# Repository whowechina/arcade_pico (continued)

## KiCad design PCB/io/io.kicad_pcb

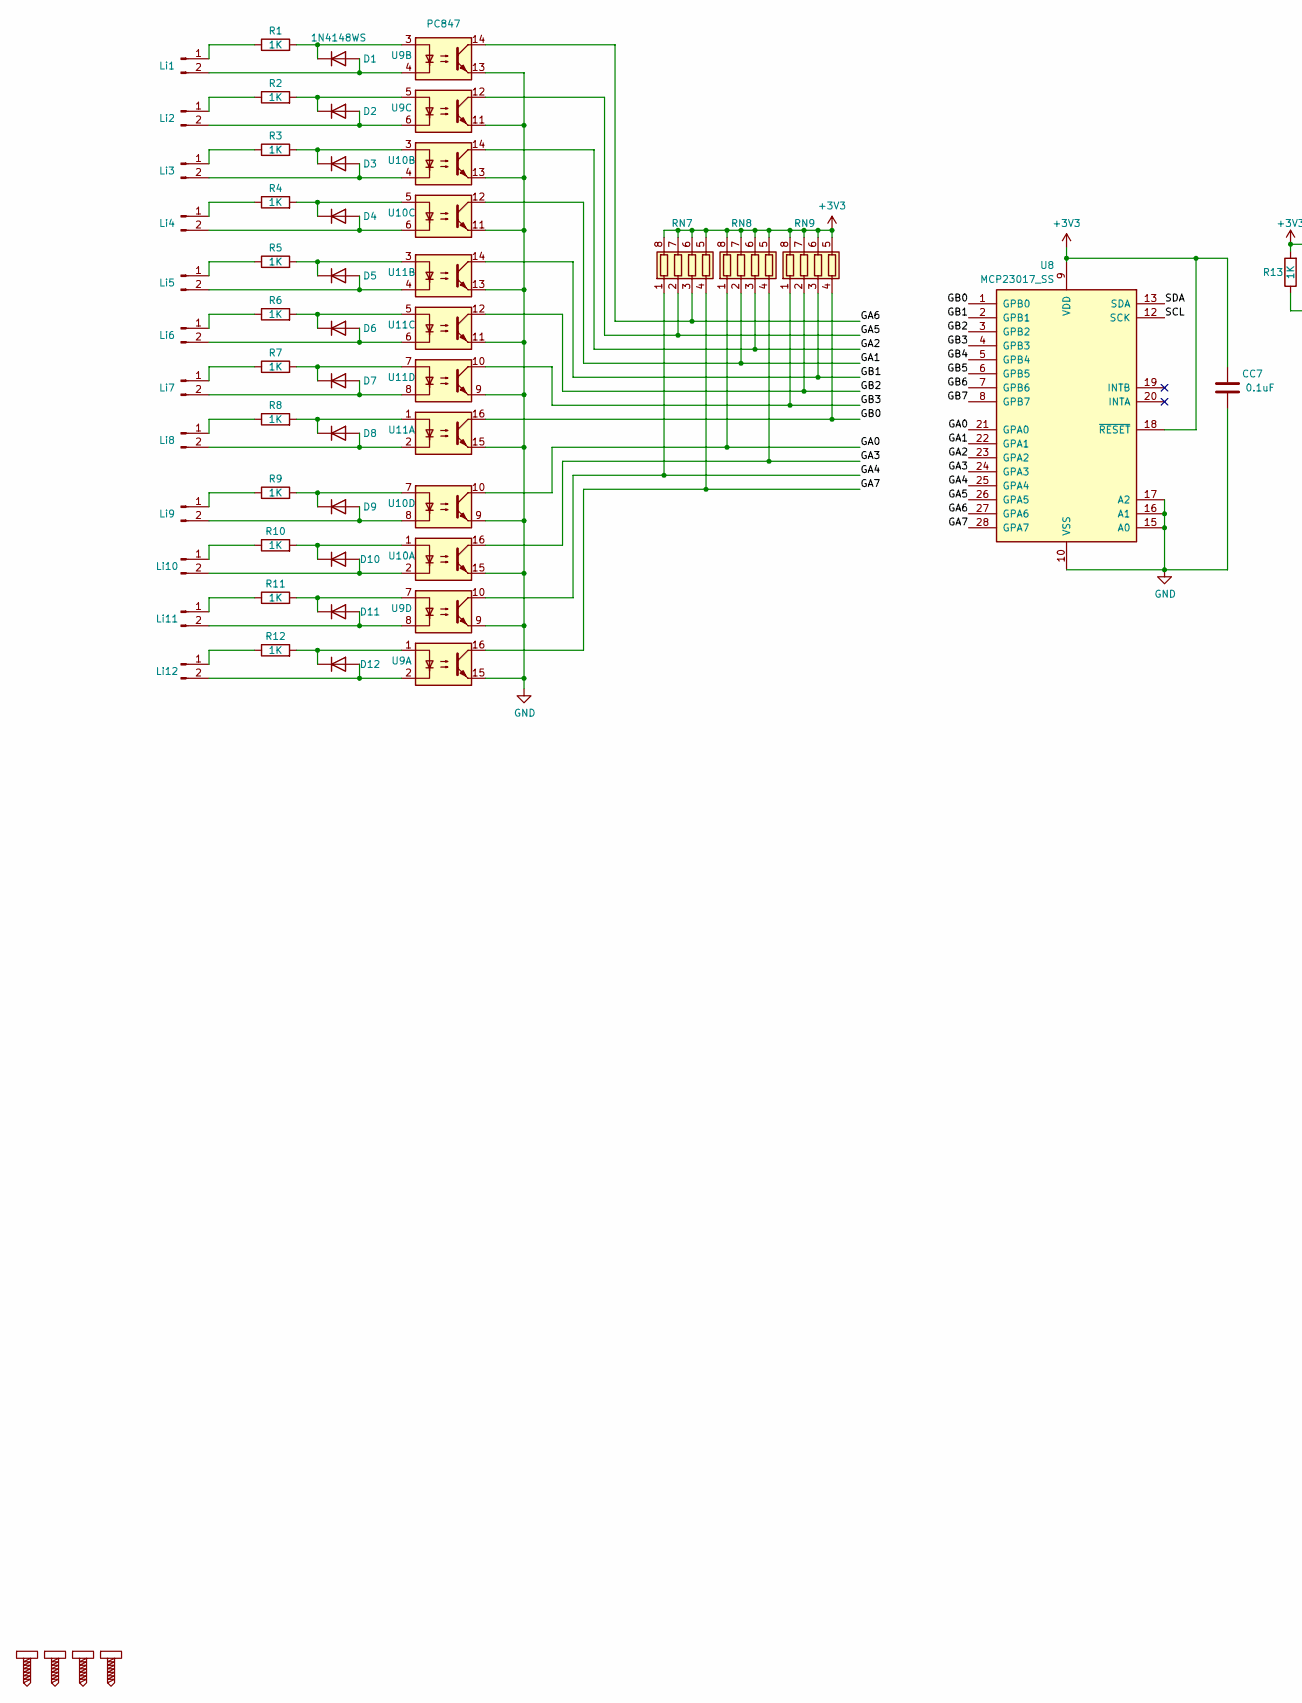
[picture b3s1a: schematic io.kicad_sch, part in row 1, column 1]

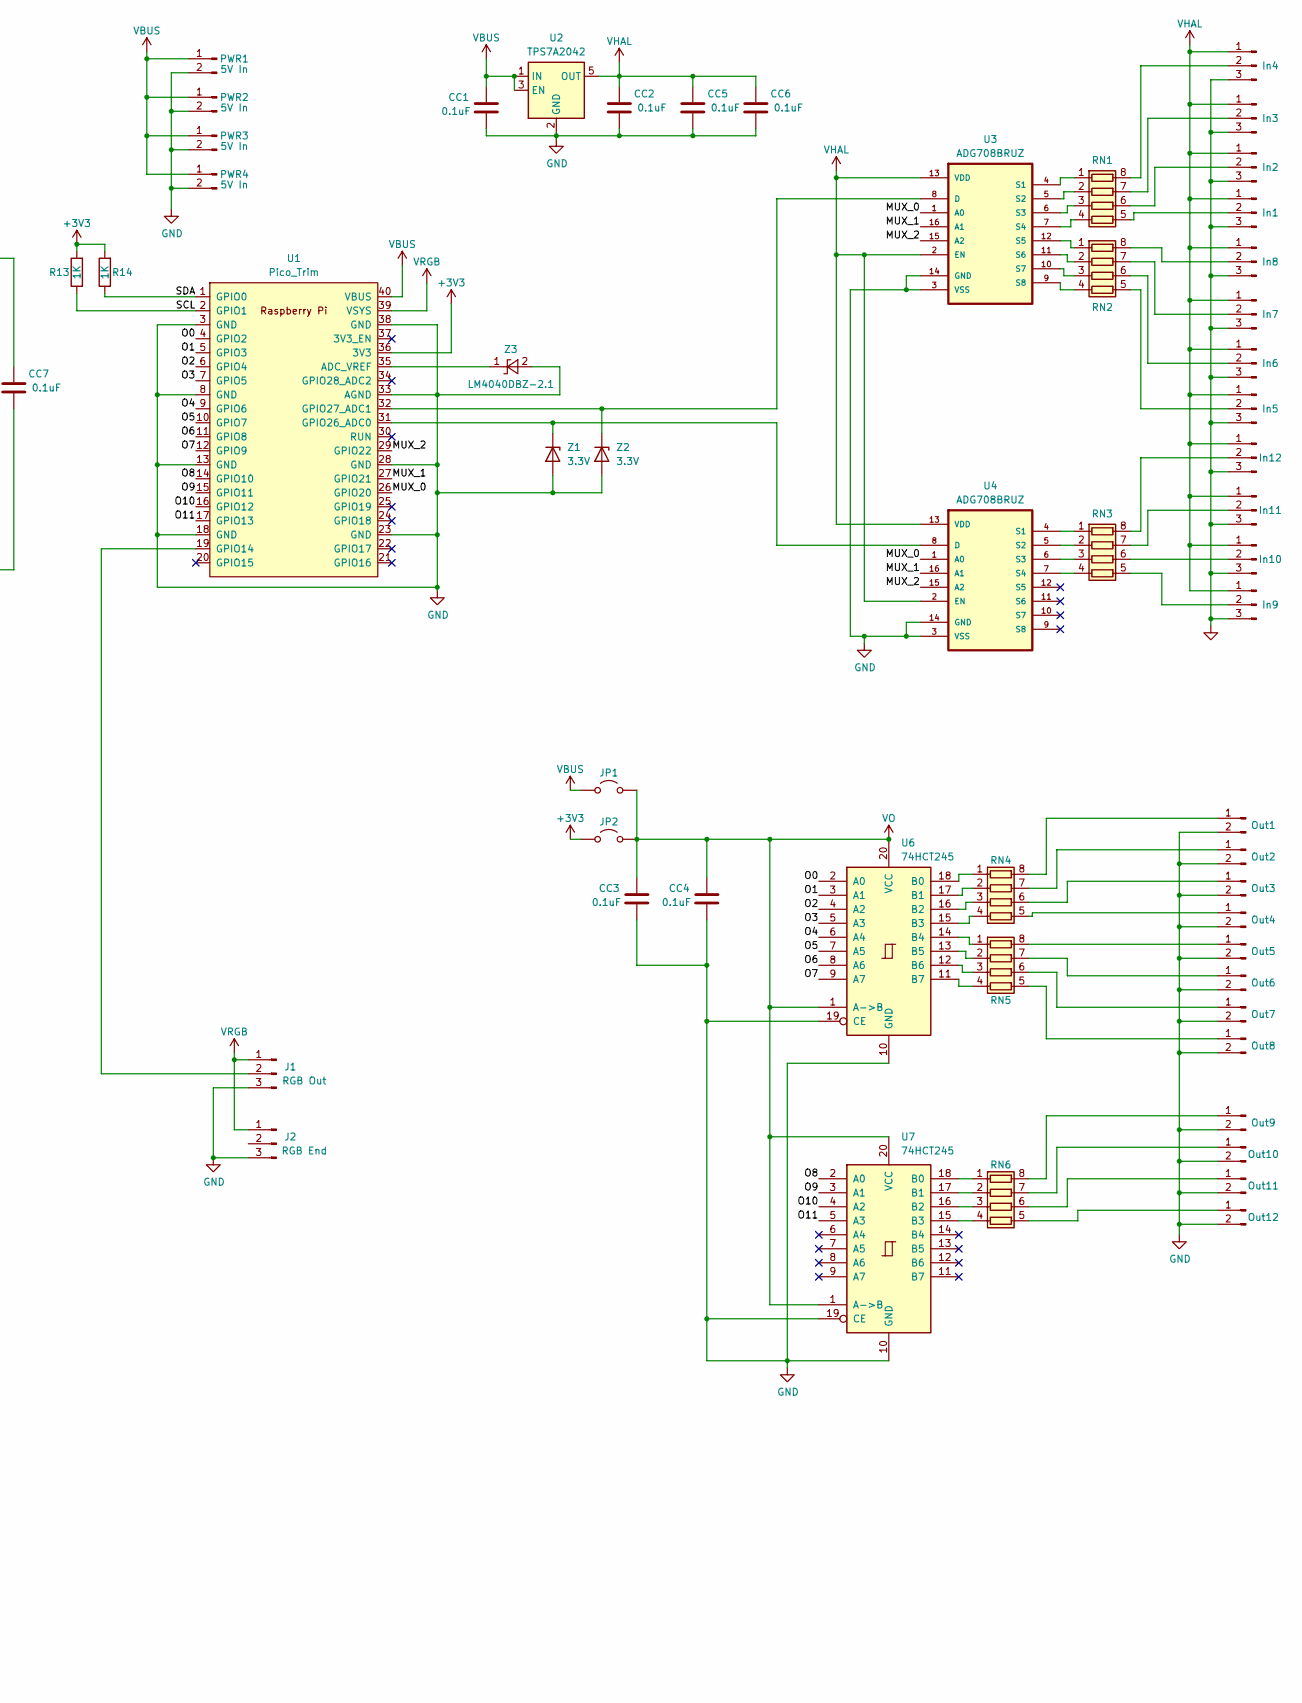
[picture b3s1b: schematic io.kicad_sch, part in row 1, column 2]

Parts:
CC1, CC2, CC3, CC4, CC5, CC6, CC7: 0.1uF; C_0603_1608Metric_Pad1.08x0.95mm_HandSolder
D1, D2, D3, D4, D5, D6, D7, D8, D9, D10, D11, D12: 1N4148WS; D_SOD-323_FAT
In1, In2, In3, In4, In5, In6, In7, In8, In9, In10, In11, In12: Conn_01x03_Pin; JST_XH_B3B-XH-A_1x03_P2.50mm_Vertical
J1: RGB Out; JST_XH_B3B-XH-A_1x03_P2.50mm_Vertical
J2: RGB End; JST_XH_B3B-XH-A_1x03_P2.50mm_Vertical
JP1: 5V; SolderJump
JP2: 3.3V; SolderJump
Li1, Li2, Li3, Li4, Li5, Li6, Li7, Li8, Li9, Li10, Li11, Li12: Conn_01x02_Pin; JST_XH_B2B-XH-A_1x02_P2.50mm_Vertical
Out1, Out2, Out3, Out4, Out5, Out6, Out7, Out8, Out9, Out10, Out11, Out12: Conn_01x02_Pin; JST_XH_B2B-XH-A_1x02_P2.50mm_Vertical
PWR1, PWR2, PWR3, PWR4: 5V In; JST_XH_B2B-XH-A_1x02_P2.50mm_Vertical
R1, R2, R3, R4, R5, R6, R7, R8, R9, R10, R11, R12: 1K; R_0805_2012Metric_Pad1.20x1.40mm_HandSolder
R13, R14: 1K; R_0603_1608Metric_Pad0.98x0.95mm_HandSolder
RN1, RN2, RN3, RN4, RN5, RN6, RN7, RN8, RN9: R_Pack04; R_Array_Convex_4x0805
S1, S2, S3, S4: M3_Screw
U1: Pico_Trim; RPi_Pico_SMD_No_USB
U2: TPS7A2042; SOT-23-5
U3, U4: ADG708BRUZ; TSSOP-16_4.4x5mm_P0.65mm
U6, U7: 74HCT245; TSSOP-20_4.4x6.5mm_P0.65mm
U8: MCP23017_SS; SSOP-28_5.3x10.2mm_P0.65mm
U9, U10, U11: PC847; SOP-16_3.9x9.9mm_P1.27mm
Z1, Z2: 3.3V; D_SOD-123F
Z3: LM4040DBZ-2.1; SOT-23-FAT

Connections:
+3V3: CC7.1, JP2.1 (A), R13.2, R14.2, RN7.5 (R4.2), RN7.6 (R3.2), RN7.7 (R2.2), RN7.8 (R1.2), RN8.5 (R4.2), RN8.6 (R3.2), RN8.7 (R2.2), RN8.8 (R1.2), RN9.5 (R4.2), RN9.6 (R3.2), RN9.7 (R2.2), RN9.8 (R1.2), U1.36 (3V3), U8.9 (VDD), U8.18 (~RESET)
/GA0: RN8.1 (R1.1), U8.21 (GPA0), U10.10
/GA1: RN8.2 (R2.1), U8.22 (GPA1), U10.12
/GA2: RN8.3 (R3.1), U8.23 (GPA2), U10.14
/GA3: RN8.4 (R4.1), U8.24 (GPA3), U10.16
/GA4: RN7.1 (R1.1), U8.25 (GPA4), U9.10
/GA5: RN7.2 (R2.1), U8.26 (GPA5), U9.12
/GA6: RN7.3 (R3.1), U8.27 (GPA6), U9.14
/GA7: RN7.4 (R4.1), U8.28 (GPA7), U9.16
/GB0: RN9.4 (R4.1), U8.1 (GPB0), U11.16
/GB1: RN9.3 (R3.1), U8.2 (GPB1), U11.14
/GB2: RN9.2 (R2.1), U8.3 (GPB2), U11.12
/GB3: RN9.1 (R1.1), U8.4 (GPB3), U11.10
/GB4: U8.5 (GPB4)
/GB5: U8.6 (GPB5)
/GB6: U8.7 (GPB6)
/GB7: U8.8 (GPB7)
/MUX_0: U1.26 (GPIO20), U3.1 (A0), U4.1 (A0)
/MUX_1: U1.27 (GPIO21), U3.16 (A1), U4.16 (A1)
/MUX_2: U1.29 (GPIO22), U3.15 (A2), U4.15 (A2)
/O0: U1.4 (GPIO2), U6.2 (A0)
/O1: U1.5 (GPIO3), U6.3 (A1)
/O2: U1.6 (GPIO4), U6.4 (A2)
/O3: U1.7 (GPIO5), U6.5 (A3)
/O4: U1.9 (GPIO6), U6.6 (A4)
/O5: U1.10 (GPIO7), U6.7 (A5)
/O6: U1.11 (GPIO8), U6.8 (A6)
/O7: U1.12 (GPIO9), U6.9 (A7)
/O8: U1.14 (GPIO10), U7.2 (A0)
/O9: U1.15 (GPIO11), U7.3 (A1)
/O10: U1.16 (GPIO12), U7.4 (A2)
/O11: U1.17 (GPIO13), U7.5 (A3)
/SCL: R13.1, U1.2 (GPIO1), U8.12 (SCK)
/SDA: R14.1, U1.1 (GPIO0), U8.13 (SDA)
GND: CC1.2, CC2.2, CC3.2, CC4.2, CC5.2, CC6.2, CC7.2, In1.3, In2.3, In3.3, In4.3, In5.3, In6.3, In7.3, In8.3, In9.3, In10.3, In11.3, In12.3, J1.3, J2.3, Out1.2, Out2.2, Out3.2, Out4.2, Out5.2, Out6.2, Out7.2, Out8.2, Out9.2, Out10.2, Out11.2, Out12.2, PWR1.2, PWR2.2, PWR3.2, PWR4.2, U1.3 (GND), U1.8 (GND), U1.13 (GND), U1.18 (GND), U1.23 (GND), U1.28 (GND), U1.33 (AGND), U1.38 (GND), U2.2 (GND), U3.3 (VSS), U3.14 (GND), U4.3 (VSS), U4.14 (GND), U6.10 (GND), U6.19 (CE), U7.10 (GND), U7.19 (CE), U8.10 (VSS), U8.15 (A0), U8.16 (A1), U8.17 (A2), U9.9, U9.11, U9.13, U9.15, U10.9, U10.11, U10.13, U10.15, U11.9, U11.11, U11.13, U11.15, Z1.2 (A), Z2.2 (A), Z3.2 (A)
unnamed: D1.2 (A), Li1.2, U9.4
unnamed: D1.1 (K), R1.2, U9.3
unnamed: D2.2 (A), Li2.2, U9.6
unnamed: D2.1 (K), R2.2, U9.5
unnamed: D3.2 (A), Li3.2, U10.4
unnamed: D3.1 (K), R3.2, U10.3
unnamed: D4.2 (A), Li4.2, U10.6
unnamed: D4.1 (K), R4.2, U10.5
unnamed: D5.2 (A), Li5.2, U11.4
unnamed: D5.1 (K), R5.2, U11.3
unnamed: D6.2 (A), Li6.2, U11.6
unnamed: D6.1 (K), R6.2, U11.5
unnamed: D7.2 (A), Li7.2, U11.8
unnamed: D7.1 (K), R7.2, U11.7
unnamed: D8.2 (A), Li8.2, U11.2
unnamed: D8.1 (K), R8.2, U11.1
unnamed: D9.2 (A), Li9.2, U10.8
unnamed: D9.1 (K), R9.2, U10.7
unnamed: D10.2 (A), Li10.2, U10.2
unnamed: D10.1 (K), R10.2, U10.1
unnamed: D11.2 (A), Li11.2, U9.8
unnamed: D11.1 (K), R11.2, U9.7
unnamed: D12.2 (A), Li12.2, U9.2
unnamed: D12.1 (K), R12.2, U9.1
unnamed: In1.2, RN1.5 (R4.2)
unnamed: In2.2, RN1.6 (R3.2)
unnamed: In3.2, RN1.7 (R2.2)
unnamed: In4.2, RN1.8 (R1.2)
unnamed: In5.2, RN2.5 (R4.2)
unnamed: In6.2, RN2.6 (R3.2)
unnamed: In7.2, RN2.7 (R2.2)
unnamed: In8.2, RN2.8 (R1.2)
unnamed: In9.2, RN3.5 (R4.2)
unnamed: In10.2, RN3.6 (R3.2)
unnamed: In11.2, RN3.7 (R2.2)
unnamed: In12.2, RN3.8 (R1.2)
unnamed: J1.2, U1.19 (GPIO14)
unnamed: Li1.1, R1.1
unnamed: Li2.1, R2.1
unnamed: Li3.1, R3.1
unnamed: Li4.1, R4.1
unnamed: Li5.1, R5.1
unnamed: Li6.1, R6.1
unnamed: Li7.1, R7.1
unnamed: Li8.1, R8.1
unnamed: Li9.1, R9.1
unnamed: Li10.1, R10.1
unnamed: Li11.1, R11.1
unnamed: Li12.1, R12.1
unnamed: Out1.1, RN4.8 (R1.2)
unnamed: Out2.1, RN4.7 (R2.2)
unnamed: Out3.1, RN4.6 (R3.2)
unnamed: Out4.1, RN4.5 (R4.2)
unnamed: Out5.1, RN5.8 (R1.2)
unnamed: Out6.1, RN5.7 (R2.2)
unnamed: Out7.1, RN5.6 (R3.2)
unnamed: Out8.1, RN5.5 (R4.2)
unnamed: Out9.1, RN6.8 (R1.2)
unnamed: Out10.1, RN6.7 (R2.2)
unnamed: Out11.1, RN6.6 (R3.2)
unnamed: Out12.1, RN6.5 (R4.2)
unnamed: RN1.1 (R1.1), U3.4 (S1)
unnamed: RN1.2 (R2.1), U3.5 (S2)
unnamed: RN1.3 (R3.1), U3.6 (S3)
unnamed: RN1.4 (R4.1), U3.7 (S4)
unnamed: RN2.1 (R1.1), U3.12 (S5)
unnamed: RN2.2 (R2.1), U3.11 (S6)
unnamed: RN2.3 (R3.1), U3.10 (S7)
unnamed: RN2.4 (R4.1), U3.9 (S8)
unnamed: RN3.1 (R1.1), U4.4 (S1)
unnamed: RN3.2 (R2.1), U4.5 (S2)
unnamed: RN3.3 (R3.1), U4.6 (S3)
unnamed: RN3.4 (R4.1), U4.7 (S4)
unnamed: RN4.1 (R1.1), U6.18 (B0)
unnamed: RN4.2 (R2.1), U6.17 (B1)
unnamed: RN4.3 (R3.1), U6.16 (B2)
unnamed: RN4.4 (R4.1), U6.15 (B3)
unnamed: RN5.1 (R1.1), U6.14 (B4)
unnamed: RN5.2 (R2.1), U6.13 (B5)
unnamed: RN5.3 (R3.1), U6.12 (B6)
unnamed: RN5.4 (R4.1), U6.11 (B7)
unnamed: RN6.1 (R1.1), U7.18 (B0)
unnamed: RN6.2 (R2.1), U7.17 (B1)
unnamed: RN6.3 (R3.1), U7.16 (B2)
unnamed: RN6.4 (R4.1), U7.15 (B3)
unnamed: U1.35 (ADC_VREF), Z3.1 (K)
unnamed: U1.31 (GPIO26_ADC0), U4.8 (D), Z1.1 (K)
unnamed: U1.32 (GPIO27_ADC1), U3.8 (D), Z2.1 (K)
VBUS: CC1.1, JP1.1 (A), PWR1.1, PWR2.1, PWR3.1, PWR4.1, U1.40 (VBUS), U2.1 (IN), U2.3 (EN)
VHAL: CC2.1, CC5.1, CC6.1, In1.1, In2.1, In3.1, In4.1, In5.1, In6.1, In7.1, In8.1, In9.1, In10.1, In11.1, In12.1, U2.5 (OUT), U3.2 (EN), U3.13 (VDD), U4.2 (EN), U4.13 (VDD)
VO: CC3.1, CC4.1, JP1.2 (B), JP2.2 (B), U6.1 (A->B), U6.20 (VCC), U7.1 (A->B), U7.20 (VCC)
VRGB: J1.1, J2.1, U1.39 (VSYS)

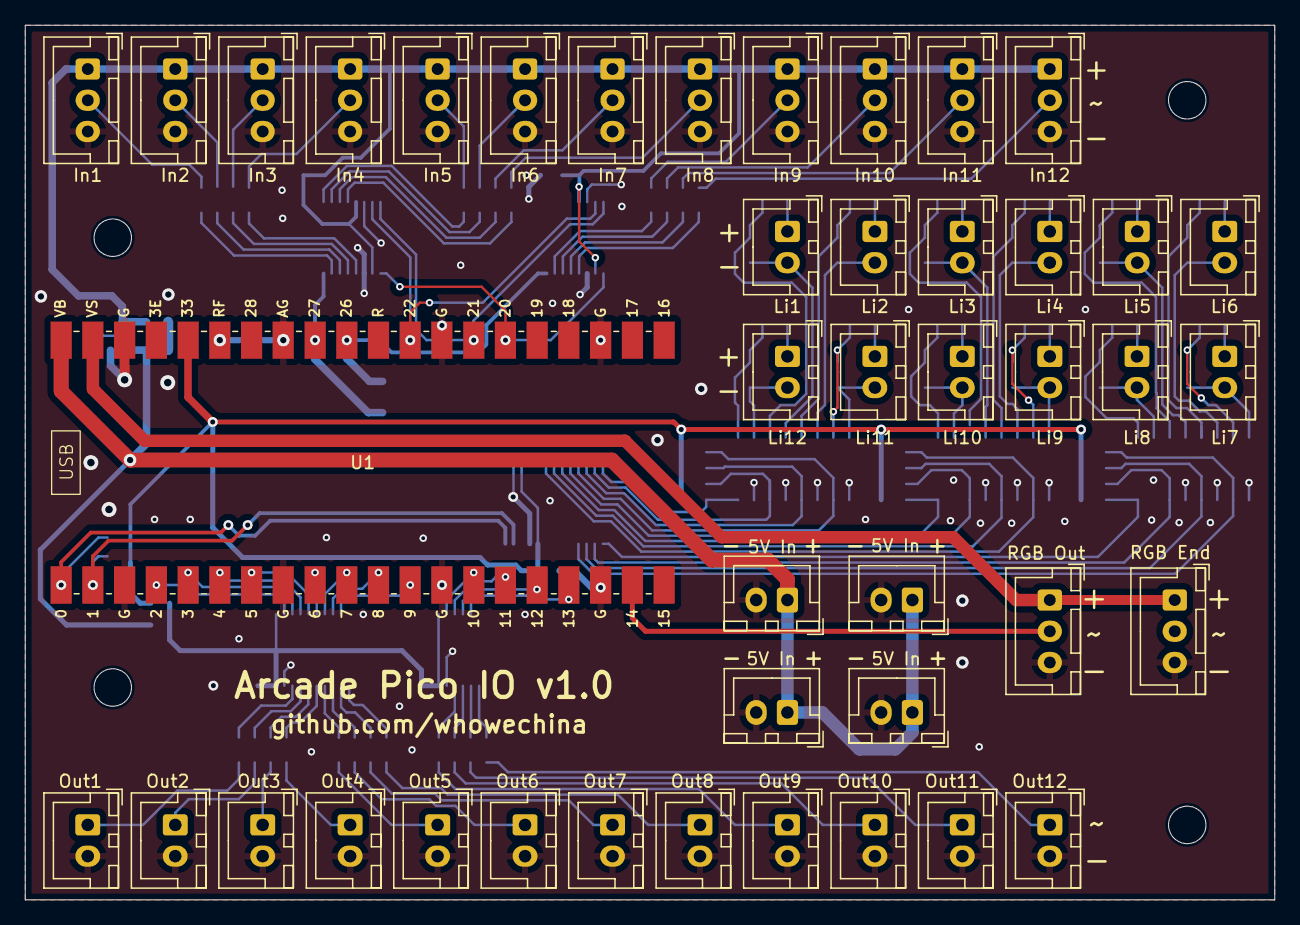
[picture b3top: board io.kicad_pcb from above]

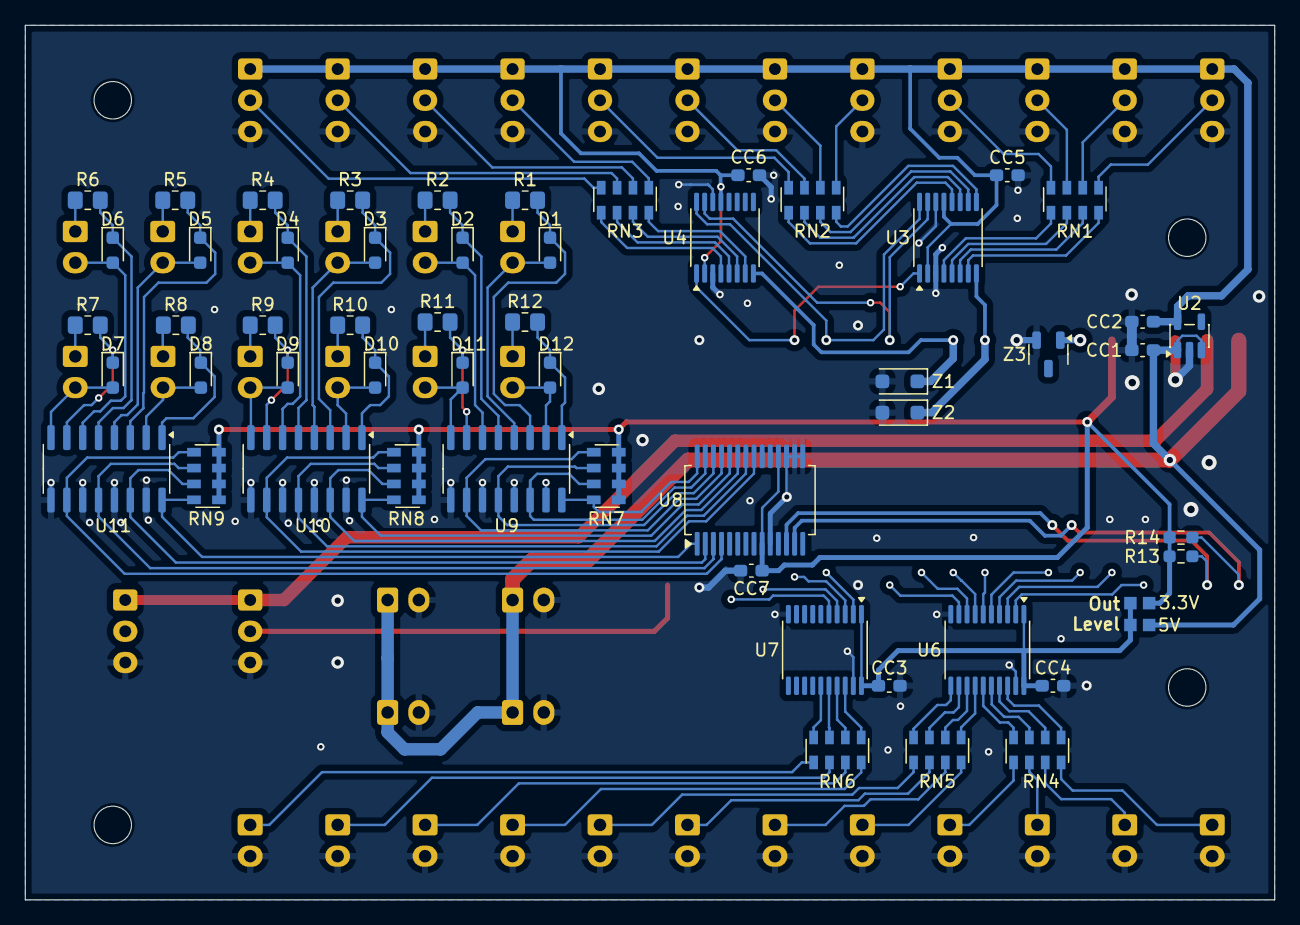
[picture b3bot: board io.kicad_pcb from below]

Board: 2 copper layers, 100.0 x 70.0 mm, 103 parts (56 on the bottom side), 123 nets.

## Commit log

2025-12-19 Button PCB v1.0
2025-12-19 IO PCB, progress 50%
2025-12-26 Button PCB v1.0 rc3
2025-12-26 IO Board v1.0 rc0
2025-12-26 Some early doc
2026-01-01 Doc in progress
2026-01-01 Button and IO8 PCB
2026-01-01 PCB v1.0
2026-01-01 Firmware initial upload
2026-01-01 3D print files
2026-01-01 Readme en almost finished
2026-01-01 Fix the link
2026-01-02 Better screw clearance
2026-01-02 Use cases in README
2026-01-03 Some format optimization
2026-01-04 PCB version for hotswap
2026-01-04 Remove the abandoned IO PCB
2026-01-04 Add reference to choc socket
2026-01-04 Update feature description
2026-01-04 README in cn
2026-01-09 Clarification on IO board
2026-01-09 Firmware kinda works
2026-01-13 Button PCB DIP LED version
2026-01-21 Fix SW1hotswap footprint
